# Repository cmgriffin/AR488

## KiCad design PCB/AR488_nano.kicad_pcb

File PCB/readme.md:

# Minimal AR488 PCB

## Summary
This is a simple PCB that implements the minimum required circuitry for the AR488 using an Arduino Nano. In addtion this PCB was designed to be single sided with top copper for ease of fabrication on a cheap CNC router (1610 Pro). A capacitor in series with a slide switch was added to the Arduino Nano reset pin in order to disable to Arduino serial DTR reset function. 

## Fabrication
Flatcam was use to prepare all gcode based on the PCB gerbers/excellon. Since only top copper was used, no flipping/mirroring in flatcam was needed. Grblcontrol  (Candle) was used to send the gcode to the router. For isolation routing a 0.1mm 20deg engraver was used with cut depth of 0.12mm. The traces and spacing used in the design are close to the router's capability limits, and height mapping is absolutely required to acheive usable results. For holes and the cutout, a 0.8mm endmill was used with 0.8mm being the minimum hole size that was milled.

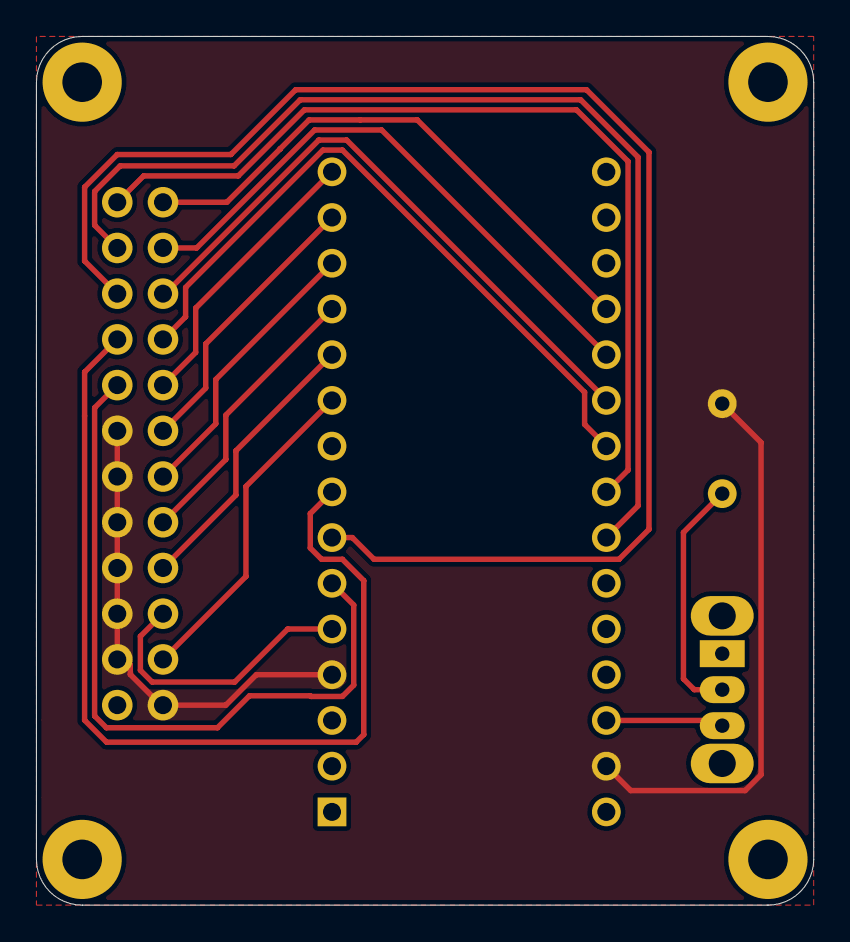
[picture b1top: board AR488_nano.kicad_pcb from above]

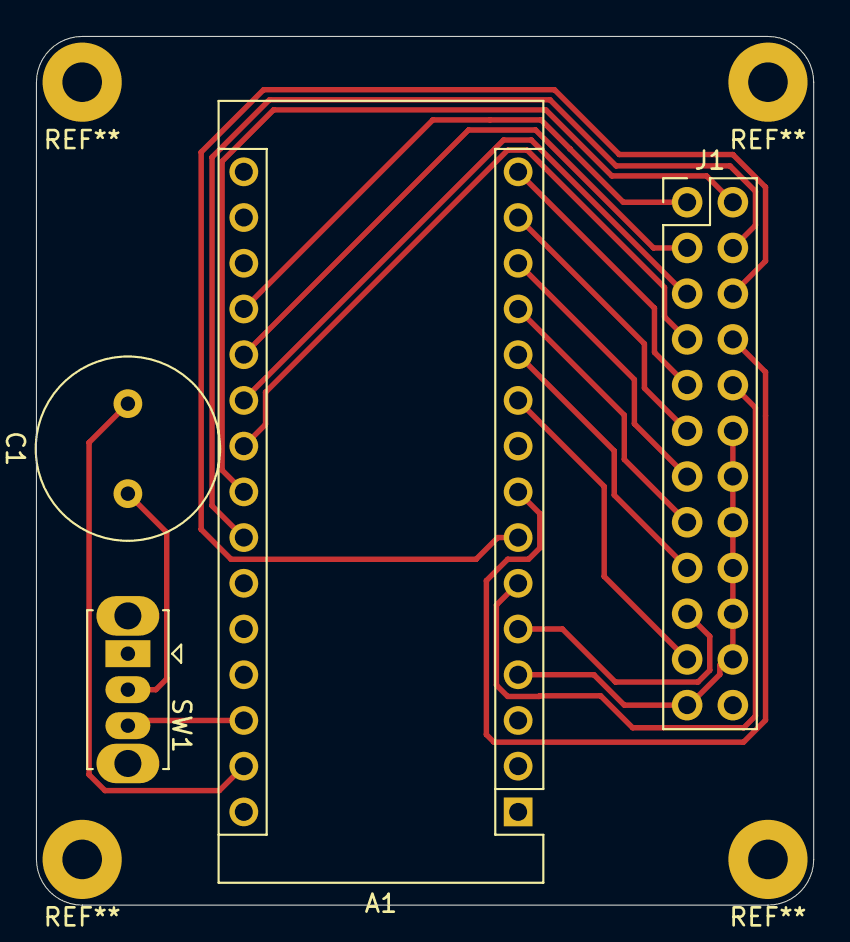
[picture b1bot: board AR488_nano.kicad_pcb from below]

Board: 2 copper layers, 43.2 x 48.3 mm, 4 parts (4 on the bottom side), 19 nets.

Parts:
A1: Arduino_Nano_v3.x; Arduino_Nano
C1: C; C_Radial_D10.0mm_H12.5mm_P5.00mm
J1: Conn_02x12_Top_Bottom; PinHeader_2x12_P2.54mm_Vertical_Top_Bottom
SW1: SW_SPDT; SW_Slide_1P2T_CK_OS102011MS2Q

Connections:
/ATN: A1.10, J1.11
/DAV: A1.14, J1.6
/DIO1: A1.19, J1.1
/DIO2: A1.20, J1.2
/DIO3: A1.21, J1.3
/DIO4: A1.22, J1.4
/DIO5: A1.23, J1.13
/DIO6: A1.24, J1.14
/DIO7: A1.7, J1.15
/DIO8: A1.8, J1.16
/EOI: A1.15, J1.5
/IFC: A1.11, J1.9
/NDAC: A1.12, J1.8
/NRFD: A1.13, J1.7
/NRST: A1.28, SW1.3
/REN: A1.6, J1.17
/SRQ: A1.5, J1.10
GND: A1.4, A1.29, C1.2, J1.12, J1.18, J1.19, J1.20, J1.21, J1.22, J1.23
unnamed: C1.1, SW1.2

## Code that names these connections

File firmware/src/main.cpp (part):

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   GPIB pins 10 and 18-24 are connected to GND
   GPIB pin 12 should be connected to the cable shield (might be n/c)
   Pin mapping follows the layout originally used by Emanuelle Girlando, but adds
   the SRQ line (GPIB 10) on pin 2 and the REN line (GPIB 17) on pin 13. The program
   should therefore be compatible with the original interface design but for full
   functionality will need the remaining two pins to be connected.
   For further information about the AR488 see:
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bool rEoi = false;    // Read eoi requested
bool rEbt = false;    // Read with specified terminator character
bool isQuery = false; // Direct instrument command is a query
uint8_t tranBrk = 0;  // Transmission break on 1=++, 2=EOI, 3=ATN 4=UNL
uint8_t eByte = 0;    // Termination character

// Device mode - send data
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      }
    }
    // Wait for instrument ready
    Wait_on_pin_state(HIGH, NRFD, AR488.rtmo);
    // Set GPIB control lines to controller read mode
    setGpibControls(CLAS);

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  }

  // Wait for DAV to go LOW indicating talker has finished setting data lines..
  if (Wait_on_pin_state(LOW, DAV, AR488.rtmo))
  {
    if (isVerb)
      arSerial->println(F("gpibReadByte: timeout waiting for DAV to go LOW"));
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  setGpibState(0b00000010, 0b00000010, 0);

  // Wait for DAV to go HIGH indicating data no longer valid (i.e. transfer complete)
  if (Wait_on_pin_state(HIGH, DAV, AR488.rtmo))
  {
    if (isVerb)
      arSerial->println(F("gpibReadByte: timeout waiting DAV to go HIGH"));
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bool gpibWriteByteHandshake(uint8_t db)
{
  // Wait for NDAC to go LOW (indicating that devices are at attention)
  if (Wait_on_pin_state(LOW, NDAC, AR488.rtmo))
  {
    if (isVerb)
      arSerial->println(F("gpibWriteByte: timeout waiting for receiver attention [NDAC asserted]"));
    return true;
  }
  // Wait for NRFD to go HIGH (indicating that receiver is ready)
  if (Wait_on_pin_state(HIGH, NRFD, AR488.rtmo))
  {
    if (isVerb)
      arSerial->println(F("gpibWriteByte: timeout waiting for receiver ready - [NRFD unasserted]"));
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  setGpibState(0b00000000, 0b00001000, 0);

  // Wait for NRFD to go LOW (receiver accepting data)
  if (Wait_on_pin_state(LOW, NRFD, AR488.rtmo))
  {
    if (isVerb)
      arSerial->println(F("gpibWriteByte: timeout waiting for data to be accepted - [NRFD asserted]"));
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  }

  // Wait for NDAC to go HIGH (data accepted)
  if (Wait_on_pin_state(HIGH, NDAC, AR488.rtmo))
  {
    if (isVerb)
      arSerial->println(F("gpibWriteByte: timeout waiting for data accepted signal - [NDAC unasserted]"));
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    // ATN status was asserted but now unasserted so abort
    if (atnStat && (digitalRead(ATN) == HIGH))
      return true;
    //    if (digitalRead(EOI)==LOW) tranBrk = 2;
  }
  return false; // = no timeout therefore succeeded!
}
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
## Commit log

2021-05-31 General Reorganization
    - Created a firmware folder for the actual AR488 firmware
    - Other non-firmware source folders can then be added in the root
    - Moved pdfs to a docs folder
    - Removed most binaries and archives
2021-05-31 Converted firmware to use PlatformIO
    - Only Arduino Nano build configuration is currently included, but
    platformio enables other configurations to be added easily later on.
2021-05-31 Added PCB files
    - Design and fab files were added for a minimal PCB utilizing the
    Arduino Nano
2021-06-11 Added 3D Printable Housing
2021-06-26 Add initial version of python driver
2021-07-17 Updates based on testing to the Ar488 class
    - Added a query method that is used instead of the pyvisa resource
    query method
    * Returns a read_raw by default
    * Can be passed a function to format the output
    * Handles flushing the serial buffer to prevent issues where the buffer
    gets out of sync and would result in stale data

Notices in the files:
firmware/src/main.cpp:
Inspired by the original work of Emanuele Girlando, licensed under a Creative
Commons Attribution-NonCommercial-NoDerivatives 4.0 International License.
AR488 is Licenced under the GNU Public licence.
